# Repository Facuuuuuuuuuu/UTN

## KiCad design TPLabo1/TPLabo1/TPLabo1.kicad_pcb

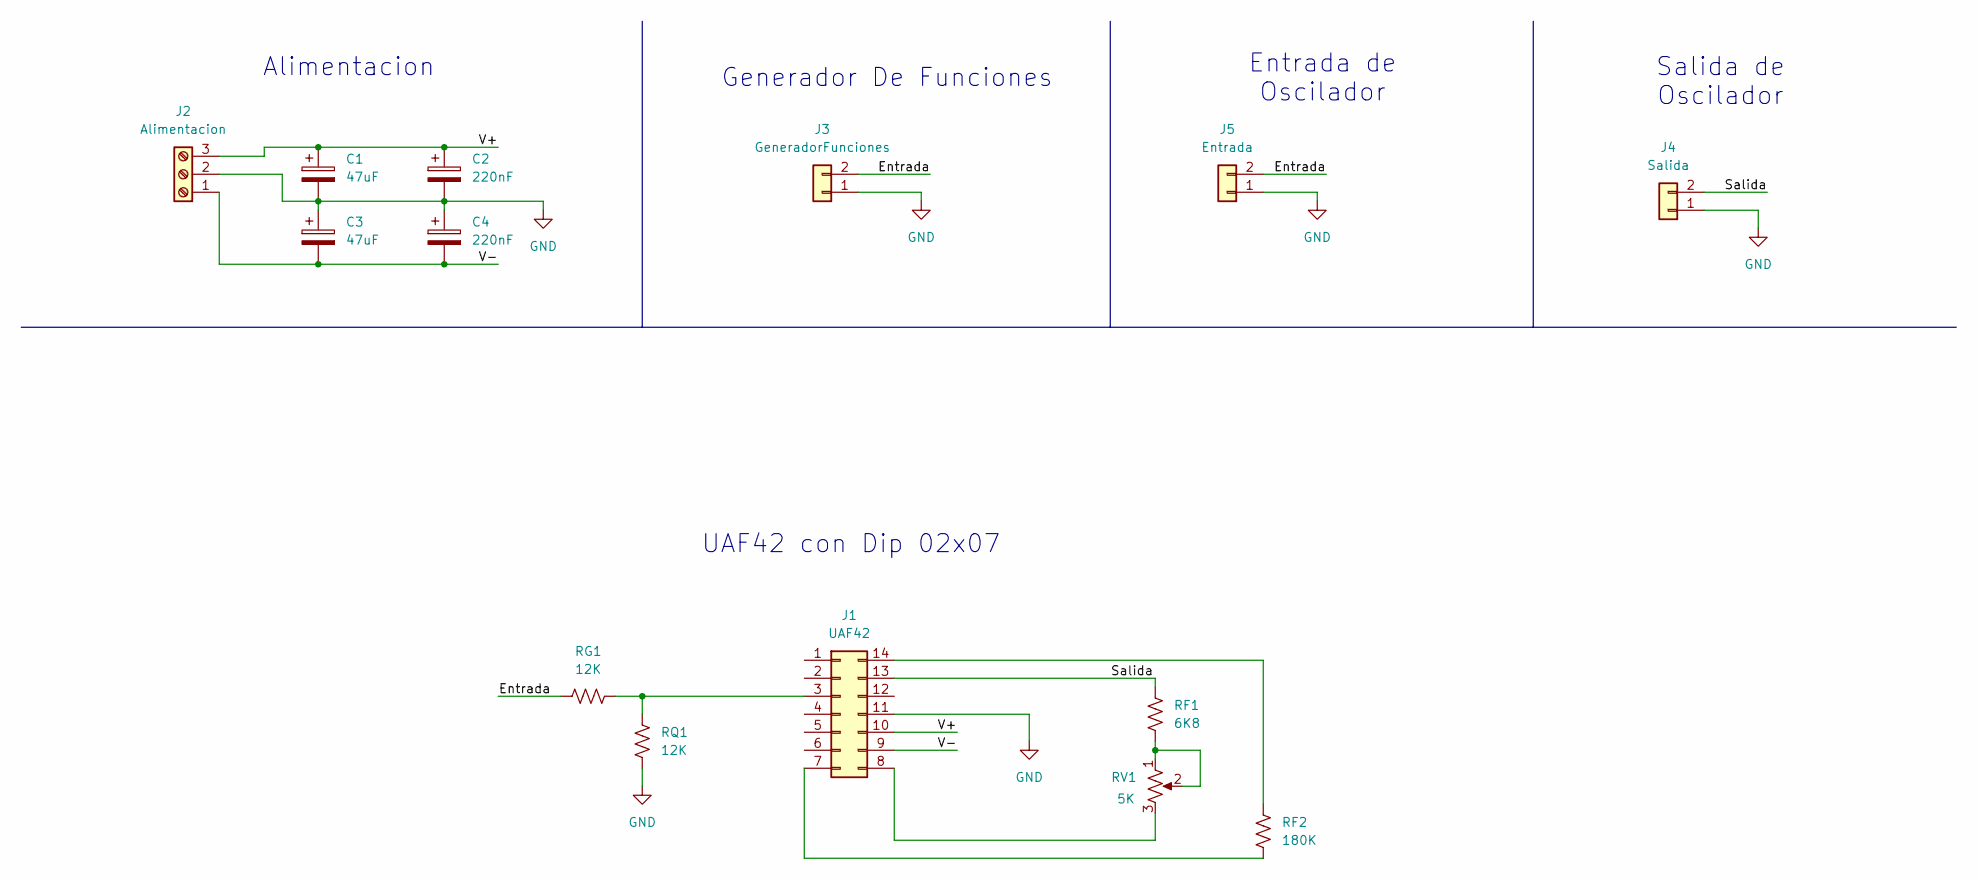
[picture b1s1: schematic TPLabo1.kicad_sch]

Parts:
C1, C3: 47uF; CP_Radial_D4.0mm_P2.00mm
C2, C4: 220nF; C_Disc_D3.0mm_W1.6mm_P2.50mm
J1: UAF42; DIP-14_W7.62mm_Socket_LongPads
J2: Alimentacion; TerminalBlock_MaiXu_MX126-5.0-03P_1x03_P5.00mm_ConModelo3D
J3: GeneradorFunciones; TerminalBlock_MaiXu_MX126-5.0-02P_1x02_P5.00mm_ConModelo3D
J4: Salida; TerminalBlock_MaiXu_MX126-5.0-02P_1x02_P5.00mm_ConModelo3D
J5: Entrada; TerminalBlock_MaiXu_MX126-5.0-02P_1x02_P5.00mm_ConModelo3D
RF1: 6K8; R_Axial_DIN0204_L3.6mm_D1.6mm_P7.62mm_Horizontal
RF2: 180K; R_Axial_DIN0204_L3.6mm_D1.6mm_P7.62mm_Horizontal
RG1: 12K; R_Axial_DIN0204_L3.6mm_D1.6mm_P7.62mm_Horizontal
RQ1: 12K; R_Axial_DIN0204_L3.6mm_D1.6mm_P7.62mm_Horizontal
RV1: 5K; Potentiometer_Bourns_3296W_Vertical

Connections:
/Entrada: J3.2, J5.2, RG1.1
/Salida: J1.13, J4.2, RF1.1
/V+: C1.1, C2.1, J1.10, J2.3
/V-: C3.2, C4.2, J1.9, J2.1
GND: C1.2, C2.2, C3.1, C4.1, J1.11, J2.2, J3.1, J4.1, J5.1, RQ1.2
unnamed: J1.3, RG1.2, RQ1.1
unnamed: J1.7, RF2.2
unnamed: J1.8, RV1.3
unnamed: J1.14, RF2.1
unnamed: RF1.2, RV1.1, RV1.2

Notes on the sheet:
UAF42 con Dip 02x07
Salida de Oscilador
Alimentacion
Generador De Funciones
Entrada de Oscilador

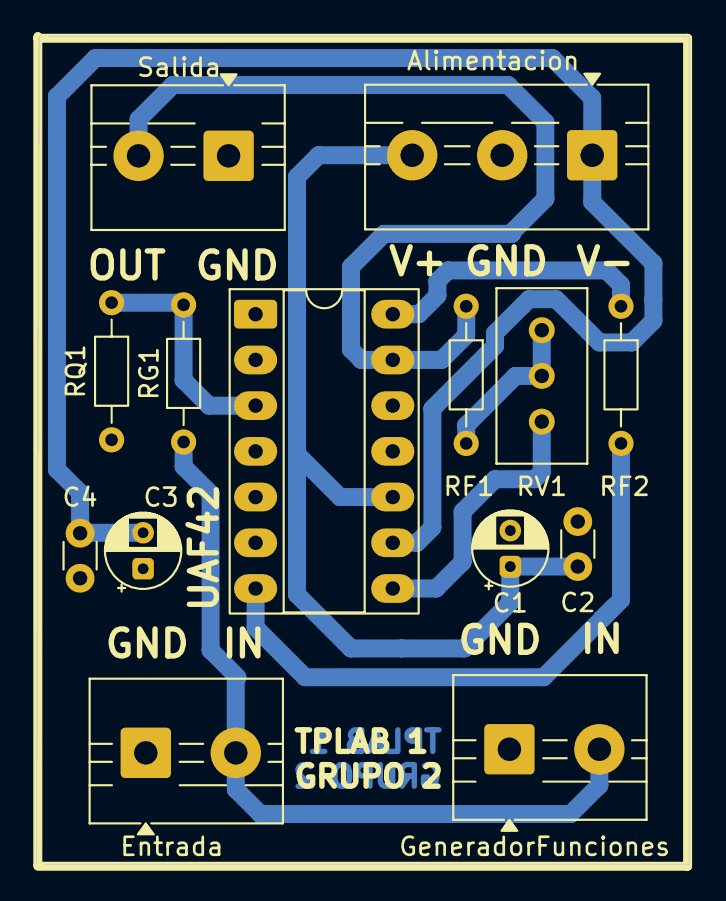
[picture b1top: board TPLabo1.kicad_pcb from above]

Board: 2 copper layers, 36.3 x 46.0 mm, 14 parts (0 on the bottom side), 10 nets.
